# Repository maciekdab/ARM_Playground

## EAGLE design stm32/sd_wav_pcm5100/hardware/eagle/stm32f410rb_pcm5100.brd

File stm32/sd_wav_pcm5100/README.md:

#### SD Card Wav player using STM32 with PCM5100 audio DAC

The project uses also Petit FAT File System Module - ELM by ChaN (http://elm-chan.org/fsw/ff/00index_p.html).

##### 3D renderings of pcb

Top view | Bottom View
------------ | -------------
 |

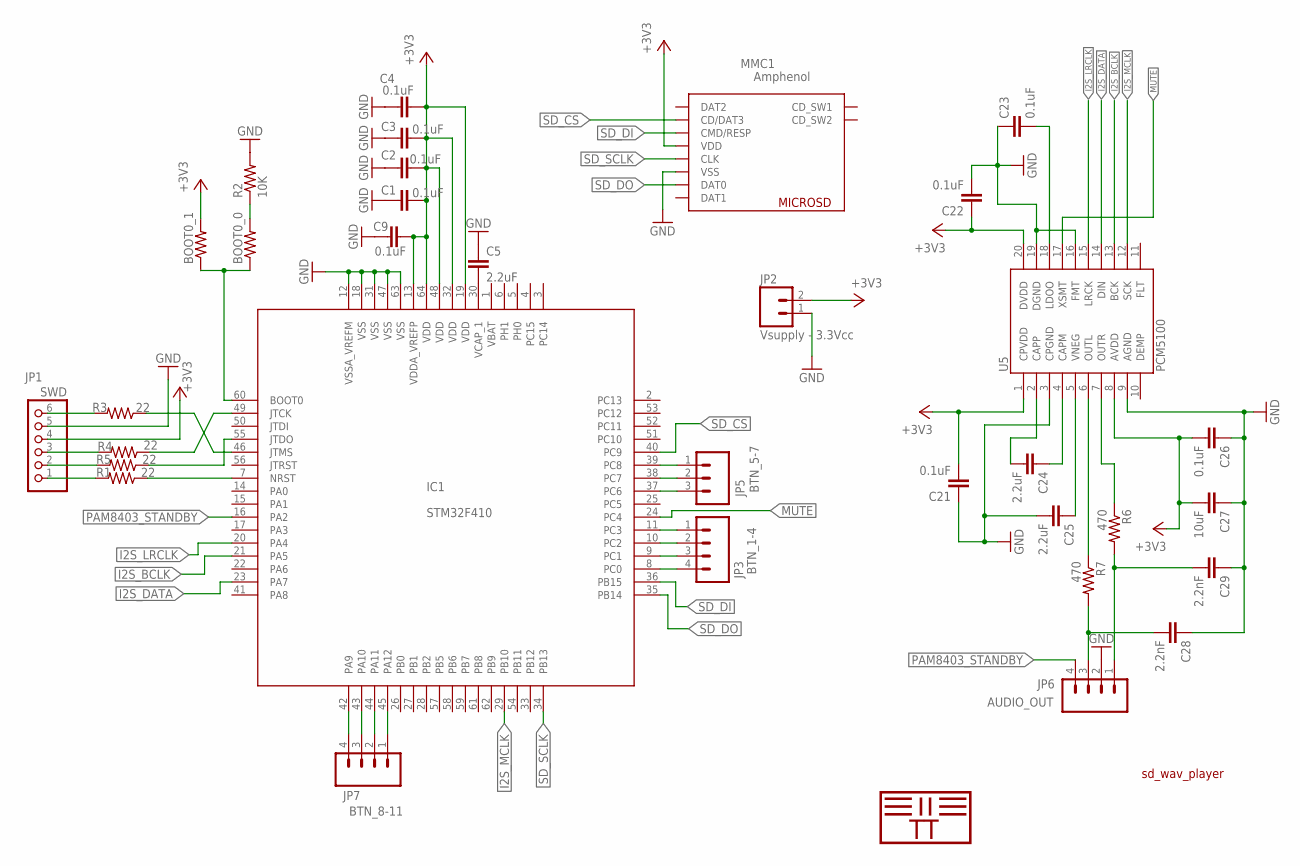
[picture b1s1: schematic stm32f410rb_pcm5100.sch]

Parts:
BOOT0_0, BOOT0_1: RESISTOR0603-RES; 0603-RES
C1, C2, C3, C4, C9, C21, C22, C23, C26: 0.1uF; 0805
C5, C24, C25: 2.2uF; 0805
C27: 10uF; 0805
C28, C29: 2.2nF; 0805
IC1: STM32F410; LQFP64
JP1: SWD; 1X06
JP2: Vsupply - 3.3Vcc; SCREWTERMINAL-3.5MM-2
JP3: BTN_1-4; SCREWTERMINAL-3.5MM-4
JP5: BTN_5-7; SCREWTERMINAL-3.5MM-3
JP6: AUDIO_OUT; SCREWTERMINAL-3.5MM-4
JP7: BTN_8-11; SCREWTERMINAL-3.5MM-4
MMC1: Amphenol; MICROSD_AMPHENOL
R1, R3, R4, R5: 22; 0805
R2: 10K; 0805
R6, R7: 470; 0805
U5: PCM5100; ROBERTSONICS_PW_R-PDSO-G20

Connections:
GND: C1.2, C2.2, C3.2, C4.2, C5.1, C9.2, C21.1, C22.2, C23.1, C25.2, C26.1, C27.1, C28.1, C29.1, IC1.12 (VSSA_VREFM), IC1.18 (VSS), IC1.31 (VSS), IC1.47 (VSS), IC1.63 (VSS), JP1.5, JP2.1, JP6.2, MMC1.VSS, R2.2, U5.3 (CPGND), U5.9 (AGND), U5.16 (FMT), U5.19 (DGND)
I2S_BCLK: IC1.21 (PA5), U5.13 (BCK)
I2S_DATA: IC1.23 (PA7), U5.14 (DIN)
I2S_LRCLK: IC1.20 (PA4), U5.15 (LRCK)
I2S_MCLK: IC1.29 (PB10), U5.12 (SCK)
LOUTL: C28.2, JP6.3, R7.2
LOUTR: C29.2, JP6.1, R6.2
MUTE: IC1.24 (PC4), U5.17 (XSMT)
unnamed: IC1.11 (PC3), JP3.1
unnamed: IC1.10 (PC2), JP3.2
unnamed: IC1.9 (PC1), JP3.3
unnamed: IC1.8 (PC0), JP3.4
unnamed: C5.2, IC1.30 (VCAP_1)
unnamed: IC1.7 (NRST), R1.1
unnamed: IC1.49 (JTCK), R4.1
unnamed: IC1.55 (JTDO), R5.1
unnamed: IC1.46 (JTMS), R3.1
unnamed: BOOT0_0.2, R2.1
unnamed: IC1.39 (PC8), JP5.1
unnamed: IC1.38 (PC7), JP5.2
unnamed: C23.2, U5.18 (LDOO)
unnamed: R6.1, U5.7 (OUTR)
unnamed: C24.2, U5.2 (CAPP)
unnamed: C24.1, U5.4 (CAPM)
unnamed: C25.1, U5.5 (VNEG)
unnamed: R7.1, U5.6 (OUTL)
unnamed: BOOT0_0.1, BOOT0_1.1, IC1.60 (BOOT0)
unnamed: IC1.37 (PC6), JP5.3
unnamed: IC1.45 (PA12), JP7.1
unnamed: IC1.44 (PA11), JP7.2
unnamed: IC1.43 (PA10), JP7.3
unnamed: IC1.42 (PA9), JP7.4
unnamed: JP1.6, R3.2
unnamed: JP1.3, R4.2
unnamed: JP1.2, R5.2
unnamed: JP1.1, R1.2
PAM8403_STANDBY: IC1.16 (PA2), JP6.4
SD_CS: IC1.40 (PC9), MMC1.CD/DAT3
SD_DI: IC1.36 (PB15), MMC1.CMD/RESP
SD_DO: IC1.35 (PB14), MMC1.DAT0
SD_SCLK: IC1.34 (PB13), MMC1.CLK
VCC: BOOT0_1.2, C1.1, C2.1, C3.1, C4.1, C9.1, C21.2, C22.1, C26.2, C27.2, IC1.13 (VDDA_VREFP), IC1.19 (VDD), IC1.32 (VDD), IC1.48 (VDD), IC1.64 (VDD), JP1.4, JP2.2, MMC1.VDD, U5.1 (CPVDD), U5.8 (AVDD), U5.20 (DVDD)

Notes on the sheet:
sd_wav_player

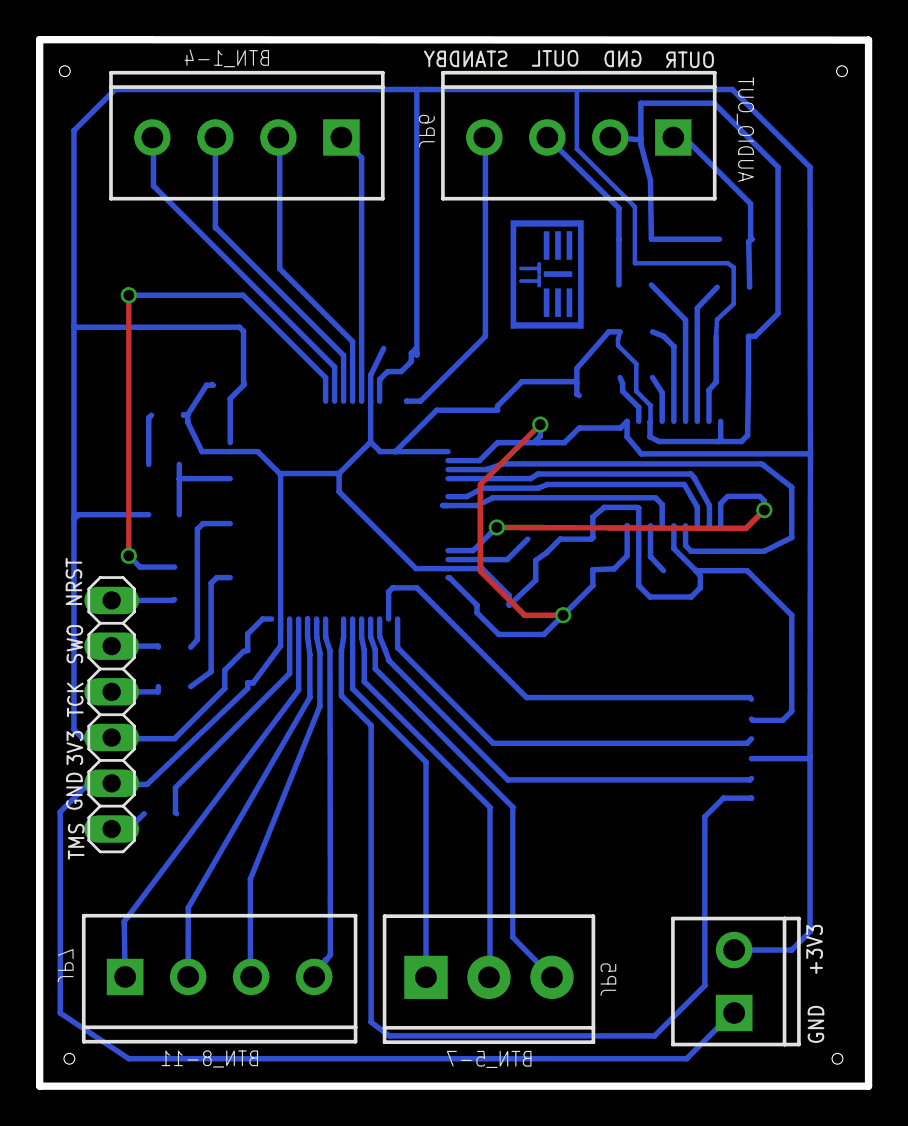
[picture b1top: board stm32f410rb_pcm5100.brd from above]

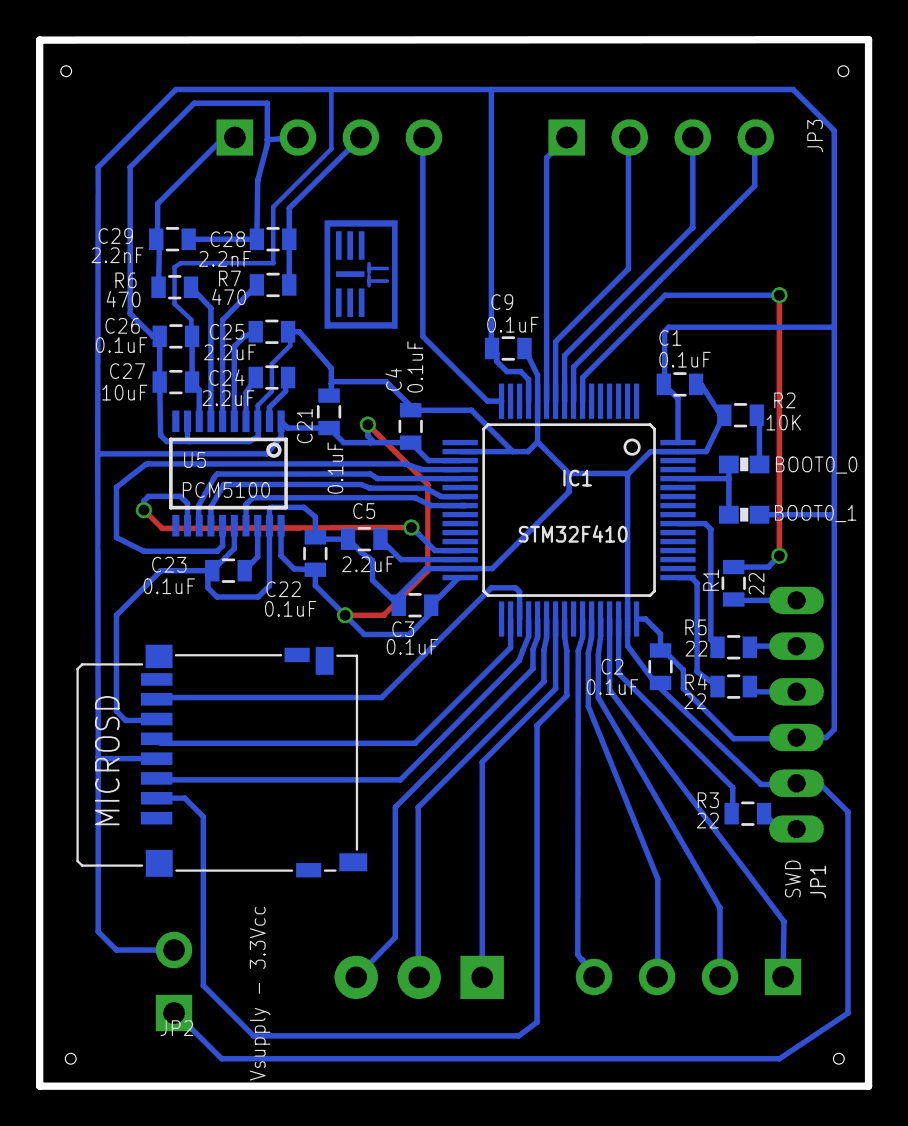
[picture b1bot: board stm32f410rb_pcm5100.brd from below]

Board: 2 copper layers, 46.1 x 58.1 mm, 33 parts (27 on the bottom side), 42 nets.

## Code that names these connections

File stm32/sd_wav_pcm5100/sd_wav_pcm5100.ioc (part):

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Mcu.Name=STM32F410R(8-B)Tx
Mcu.Package=LQFP64
Mcu.UserName=STM32F410RBTx
PA1.GPIOParameters=GPIO_Label
PA1.GPIO_Label=PAM8403_MUTE
PA1.Signal=GPIO_Output
PA10.GPIOParameters=GPIO_PuPd,GPIO_Label,GPIO_ModeDefaultEXTI
PA10.GPIO_Label=BTN_9
PA10.GPIO_ModeDefaultEXTI=GPIO_MODE_IT_FALLING
PA10.GPIO_PuPd=GPIO_PULLUP
PA10.Signal=GPXTI10
PA11.GPIOParameters=GPIO_PuPd,GPIO_Label,GPIO_ModeDefaultEXTI
PA11.GPIO_Label=BTN_10
PA11.GPIO_ModeDefaultEXTI=GPIO_MODE_IT_FALLING
PA11.GPIO_PuPd=GPIO_PULLUP
PA11.Signal=GPXTI11
PA12.GPIOParameters=GPIO_PuPd,GPIO_Label,GPIO_ModeDefaultEXTI
PA12.GPIO_Label=BTN_11
PA12.GPIO_ModeDefaultEXTI=GPIO_MODE_IT_FALLING
PA12.GPIO_PuPd=GPIO_PULLUP
PA12.Signal=GPXTI12
PA13.GPIOParameters=GPIO_Label
PA13.GPIO_Label=TMS
PA13.Mode=Trace_Asynchronous_SW
PA13.Signal=SYS_JTMS-SWDIO
PA14.GPIOParameters=GPIO_Label
PA14.GPIO_Label=TCK
PA14.Mode=Trace_Asynchronous_SW
PA14.Signal=SYS_JTCK-SWCLK
PA2.GPIOParameters=GPIO_Speed,GPIO_Label
PA2.GPIO_Label=PAM8403_STANDBY
PA2.GPIO_Speed=GPIO_SPEED_FREQ_LOW
PA2.Signal=GPIO_Output
PA4.GPIOParameters=GPIO_Speed,GPIO_Label
PA4.GPIO_Label=I2S_LRCLK
PA4.GPIO_Speed=GPIO_SPEED_FREQ_MEDIUM
PA4.Mode=Half_Duplex_Master
PA4.Signal=I2S1_WS
PA5.GPIOParameters=GPIO_Speed,GPIO_Label
PA5.GPIO_Label=I2S_BCLK
PA5.GPIO_Speed=GPIO_SPEED_FREQ_MEDIUM
PA5.Mode=Half_Duplex_Master
PA5.Signal=I2S1_CK
PA7.GPIOParameters=GPIO_Speed,GPIO_Label
PA7.GPIO_Label=I2S_DATA
PA7.GPIO_Speed=GPIO_SPEED_FREQ_MEDIUM
PA7.Mode=Half_Duplex_Master
PA7.Signal=I2S1_SD
PA9.GPIOParameters=GPIO_PuPd,GPIO_Label,GPIO_ModeDefaultEXTI
PA9.GPIO_Label=BTN_8
PA9.GPIO_ModeDefaultEXTI=GPIO_MODE_IT_FALLING
PA9.GPIO_PuPd=GPIO_PULLUP
PA9.Signal=GPXTI9
PB10.GPIOParameters=GPIO_Speed,GPIO_Label
PB10.GPIO_Label=I2S_MCLK
PB10.GPIO_Speed=GPIO_SPEED_FREQ_MEDIUM
PB10.Mode=Master_Clock_Activated
PB10.Signal=I2S1_MCK
PB13.GPIOParameters=GPIO_Label
PB13.GPIO_Label=SD_SCLK
PB13.Mode=Full_Duplex_Master
PB13.Signal=SPI2_SCK
PB14.GPIOParameters=GPIO_Label
PB14.GPIO_Label=SD_DO
PB14.Mode=Full_Duplex_Master
PB14.Signal=SPI2_MISO
PB15.GPIOParameters=GPIO_PuPd,GPIO_Label
PB15.GPIO_Label=SD_DI
PB15.GPIO_PuPd=GPIO_PULLUP
PB15.Mode=Full_Duplex_Master
PB15.Signal=SPI2_MOSI
PB3.GPIOParameters=GPIO_Label
PB3.GPIO_Label=SWO
PB3.Mode=Trace_Asynchronous_SW
PB3.Signal=SYS_JTDO-SWO
PC0.GPIOParameters=GPIO_PuPd,GPIO_Label,GPIO_ModeDefaultEXTI
PC0.GPIO_Label=BTN_1
PC0.GPIO_ModeDefaultEXTI=GPIO_MODE_IT_FALLING
PC0.GPIO_PuPd=GPIO_PULLUP
PC0.Signal=GPXTI0
PC1.GPIOParameters=GPIO_PuPd,GPIO_Label,GPIO_ModeDefaultEXTI
PC1.GPIO_Label=BTN_2
PC1.GPIO_ModeDefaultEXTI=GPIO_MODE_IT_FALLING
PC1.GPIO_PuPd=GPIO_PULLUP
PC1.Signal=GPXTI1
PC2.GPIOParameters=GPIO_PuPd,GPIO_Label,GPIO_ModeDefaultEXTI
PC2.GPIO_Label=BTN_3
PC2.GPIO_ModeDefaultEXTI=GPIO_MODE_IT_FALLING
PC2.GPIO_PuPd=GPIO_PULLUP
PC2.Signal=GPXTI2
PC3.GPIOParameters=GPIO_PuPd,GPIO_Label,GPIO_ModeDefaultEXTI
PC3.GPIO_Label=BTN_4
PC3.GPIO_ModeDefaultEXTI=GPIO_MODE_IT_FALLING
PC3.GPIO_PuPd=GPIO_PULLUP
PC3.Signal=GPXTI3
PC4.GPIOParameters=GPIO_Speed,GPIO_Label
PC4.GPIO_Label=PCM5100_MUTE
PC4.GPIO_Speed=GPIO_SPEED_FREQ_MEDIUM
PC4.Signal=GPIO_Output
PC6.GPIOParameters=GPIO_PuPd,GPIO_Label,GPIO_ModeDefaultEXTI
PC6.GPIO_Label=BTN_5
PC6.GPIO_ModeDefaultEXTI=GPIO_MODE_IT_FALLING
PC6.GPIO_PuPd=GPIO_PULLUP
PC6.Signal=GPXTI6
PC7.GPIOParameters=GPIO_PuPd,GPIO_Label,GPIO_ModeDefaultEXTI
PC7.GPIO_Label=BTN_6
PC7.GPIO_ModeDefaultEXTI=GPIO_MODE_IT_FALLING
PC7.GPIO_PuPd=GPIO_PULLUP
PC7.Signal=GPXTI7
PC8.GPIOParameters=GPIO_PuPd,GPIO_Label,GPIO_ModeDefaultEXTI
PC8.GPIO_Label=BTN_7
PC8.GPIO_ModeDefaultEXTI=GPIO_MODE_IT_FALLING
PC8.GPIO_PuPd=GPIO_PULLUP
PC8.Signal=GPXTI8
PC9.GPIOParameters=GPIO_Label
PC9.GPIO_Label=SD_CS
PC9.Signal=GPIO_Output
RCC.HSE_VALUE=25000000
RCC.SYSCLKFreq_VALUE=100000000
RCC.SYSCLKSource=RCC_SYSCLKSOURCE_PLLCLK
board=sd_wav_pcm5100

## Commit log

2016-03-01 added cubemx project file and reorganized whole project
2016-03-01 refactorings
2016-03-01 added pinout
2016-03-01 enabled hse 8MHZ crystal clock
2016-03-16 added sd_wav project
2016-03-18 added sd wav i2s player
2016-03-18 added project readme
2016-03-30 added stm32 i2s with pcm5100
2016-03-30 added stm32 i2s with pcm5100 schematic pdf
2016-03-30 added dirtypcb gerbers
2016-03-31 refactored pcb
2016-03-31 added eagle project libs in one file
2016-03-31 updated schematics
2016-03-31 fixed board trace alignment
2016-04-01 added shenzen2u/smart-proto cam/dru files
2016-04-04 added 3d renderings
2016-04-05 added microsd model
2016-04-12 reorganized rules and gerber files
2016-04-14 stm32-pcm5100 hw 3d renderings update
2016-04-20 [sd_wav_pcm5100] some final pcb touches
2016-04-27 [stm32/sd_wav_pcm5100] added petitfs src files
2016-04-27 [stm32/sd_wav_pcm5100] added audio playing logic
2016-04-27 [stm32/sd_wav_pcm5100] fixed code generation
2016-04-27 [stm32/sd_wav_pcm5100] pcm/pwr amplifier control pins/ports refactor
2016-04-28 [stm32/sd_wav_pcm5100] SPI DI/DO lines were inversed
2016-04-28 [stm32/sd_wav_pcm5100] SPI DI/DO lines were inversed - fixed stm32 cube pin assignments
2016-04-28 [stm32/sd_wav_pcm5100] added sounds list
2016-07-26 [sd_wav_pcm5100] updated stmcube hal framework
2016-07-26 [sd_wav_pcm5100] added exti interrupt support for required buttons
2016-10-19 updated project files as stm32cubemx was upgraded
2016-11-09 ide changes
2016-12-12 updated stm32cubemx generator and re-generated code to reflect new HAL api changes
2017-03-16 updated stm32cube and F4 firmware
2017-03-16 [sd_wav_pcm5100] updated eclipse project
2017-05-04 [sd_wav_pcm5100] added audio samples
2018-02-26 updated to latest cubemx generator and moved to attolic studio
2018-10-15 added railroad crossing toy project
2018-10-15 added gitignore
2018-10-22 added cubemx project
2018-10-30 f303_k8 added swstm32 project and sleep mode
2018-10-31 fixes
2018-11-01 sleep current improvments for railroad project
2018-11-23 cubemx updates

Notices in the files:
parts and their libraries:
SparkFun-Passives: Licensing: CC v3.0 Share-Alike You are welcome to use this library for commercial purposes.
SparkFun-Connectors: Licensing: Creative Commons ShareAlike 4.0 International - https://creativecommons.org/licenses/by-sa/4.0
